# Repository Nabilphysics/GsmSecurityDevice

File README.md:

# GsmSecurityDevice
GSM(SMS &amp; Call) Based Security device by https://www.cruxbd.com 

This device receives signal from PIR motion sensor and send alert to configured number. User can configure Password, Number and Modes.

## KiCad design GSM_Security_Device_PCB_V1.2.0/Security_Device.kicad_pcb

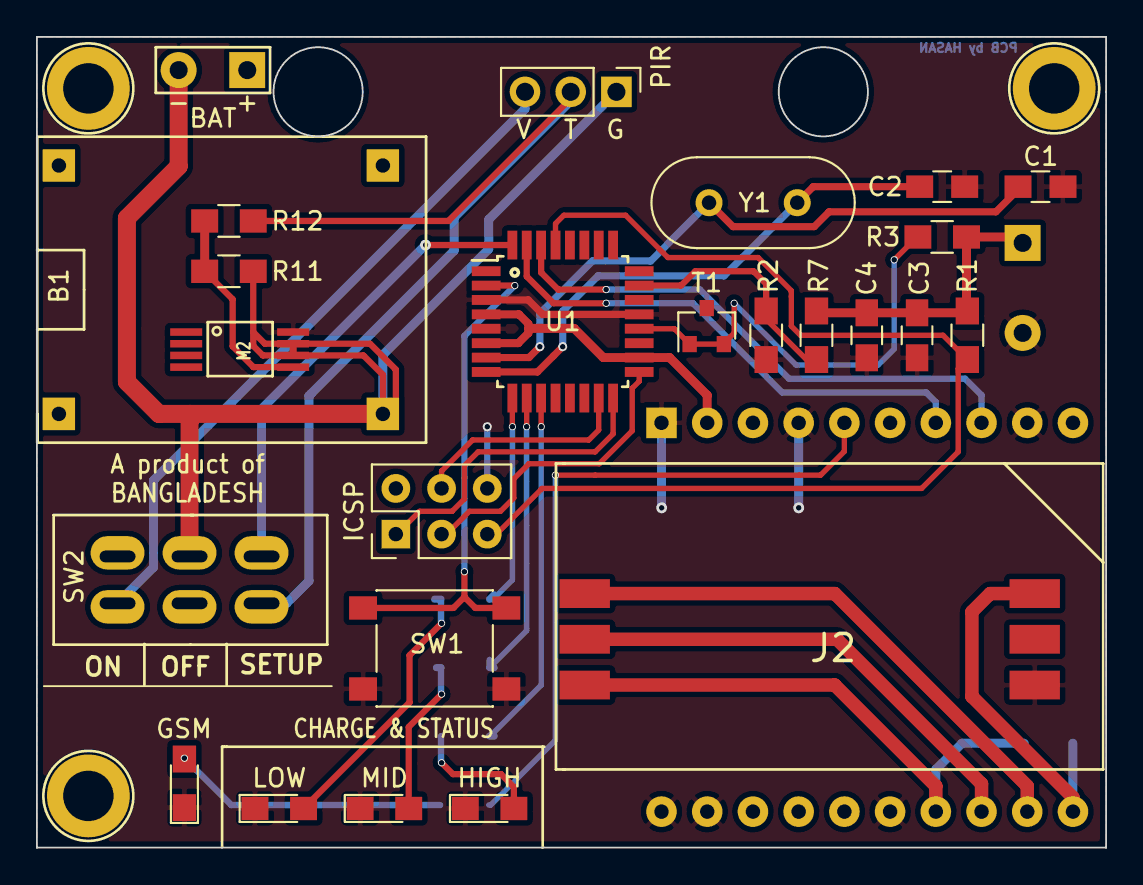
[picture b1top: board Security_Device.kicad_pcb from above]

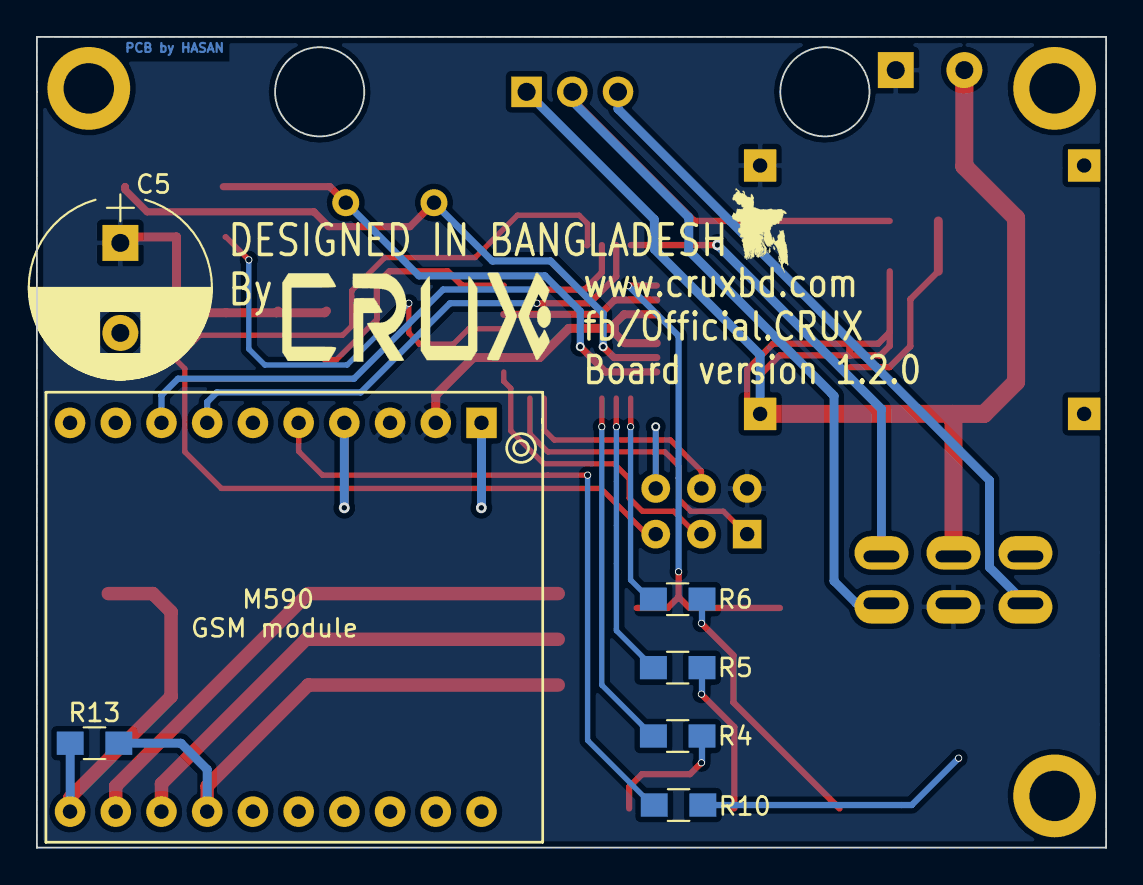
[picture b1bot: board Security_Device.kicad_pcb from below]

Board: 2 copper layers, 59.4 x 45.0 mm, 31 parts (7 on the bottom side), 29 nets.

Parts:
B1: Battery_charging_module
BAT: Battery_Pad; Battery_pad
C1, C2: 15pf; C_0805_HandSoldering
C3: 120pf; C_0805_HandSoldering
C4: 0.1uf; C_0805_HandSoldering
C5: 1000uf; CP_Radial_D10.0mm_P5.00mm
GSM: LED; LED_0805_HandSoldering
HIGH: LED; LED_0805_HandSoldering
ICSP: AVR_ICSP; ICSP_PinHeader_2x03_P2.54mm_Vertical
J2: SIM_Card; SIM Card
LOW: LED; LED_0805_HandSoldering
M2: FS8205A; TSSOP-8
M590: M590
MID: LED; LED_0805_HandSoldering
R1, R2, R7, R11, R13: 10k; R_0805_HandSoldering
R3, R4, R5, R6, R10: 1k; R_0805_HandSoldering
R12: 220R; R_0805_HandSoldering
SW1: RST; SW_SPST_PTS645
SW2: SW_2P2T_DPDTx2; DPDT SW 6 pin
T1: TL431; SOT-23
U1: ATMEGA8A-AU; TQFP-32_7x7mm_Pitch0.8mm
Y1: Crystal; Crystal_HC18-U_Vertical

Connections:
A0: R2.1, R7.1, U1.23
D2: SW2.4, U1.32
D4: SW1.2, U1.2
GND: C1.2, C2.2, C3.2, C4.2, C5.2, GSM.1, HIGH.1, ICSP.6, J2.4, LOW.1, M2.8, M590.1, M590.4, M590.9, M590.15, M590.19, M590.20, MID.1, R2.2, SW1.1, T1.3, U1.3, U1.5, U1.21
unnamed: B1.3, BAT.2, M2.6, M2.7, R11.2, SW2.5
unnamed: C1.1, U1.7, Y1.1
unnamed: C2.1, U1.8, Y1.2
unnamed: HIGH.2, R4.2
unnamed: MID.2, R5.2
unnamed: LOW.2, R6.2
unnamed: GSM.2, R10.1
unnamed: M590.5, R10.2
unnamed: M590.7, U1.31
unnamed: M590.8, U1.30
unnamed: J2.6, M590.11, R13.1
unnamed: J2.3, M590.12
unnamed: J2.2, M590.13
unnamed: J2.1, M590.14, R13.2
unnamed: ICSP.1, U1.16
unnamed: ICSP.3, U1.17
unnamed: ICSP.4, U1.15
unnamed: R12.2, SW2.3
unnamed: M2.5, R11.1, R12.1
unnamed: R3.2, T1.1, T1.2, U1.20
unnamed: R4.1, U1.11
unnamed: R5.1, U1.10
unnamed: R6.1, U1.9
RST: ICSP.5, R1.2, U1.29
VCC: B1.4, BAT.1, C3.1, C4.1, C5.1, ICSP.2, M590.2, M590.3, R1.1, R3.1, R7.2, SW2.2, U1.4, U1.6, U1.18

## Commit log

2020-08-21 PCB and Schematic
